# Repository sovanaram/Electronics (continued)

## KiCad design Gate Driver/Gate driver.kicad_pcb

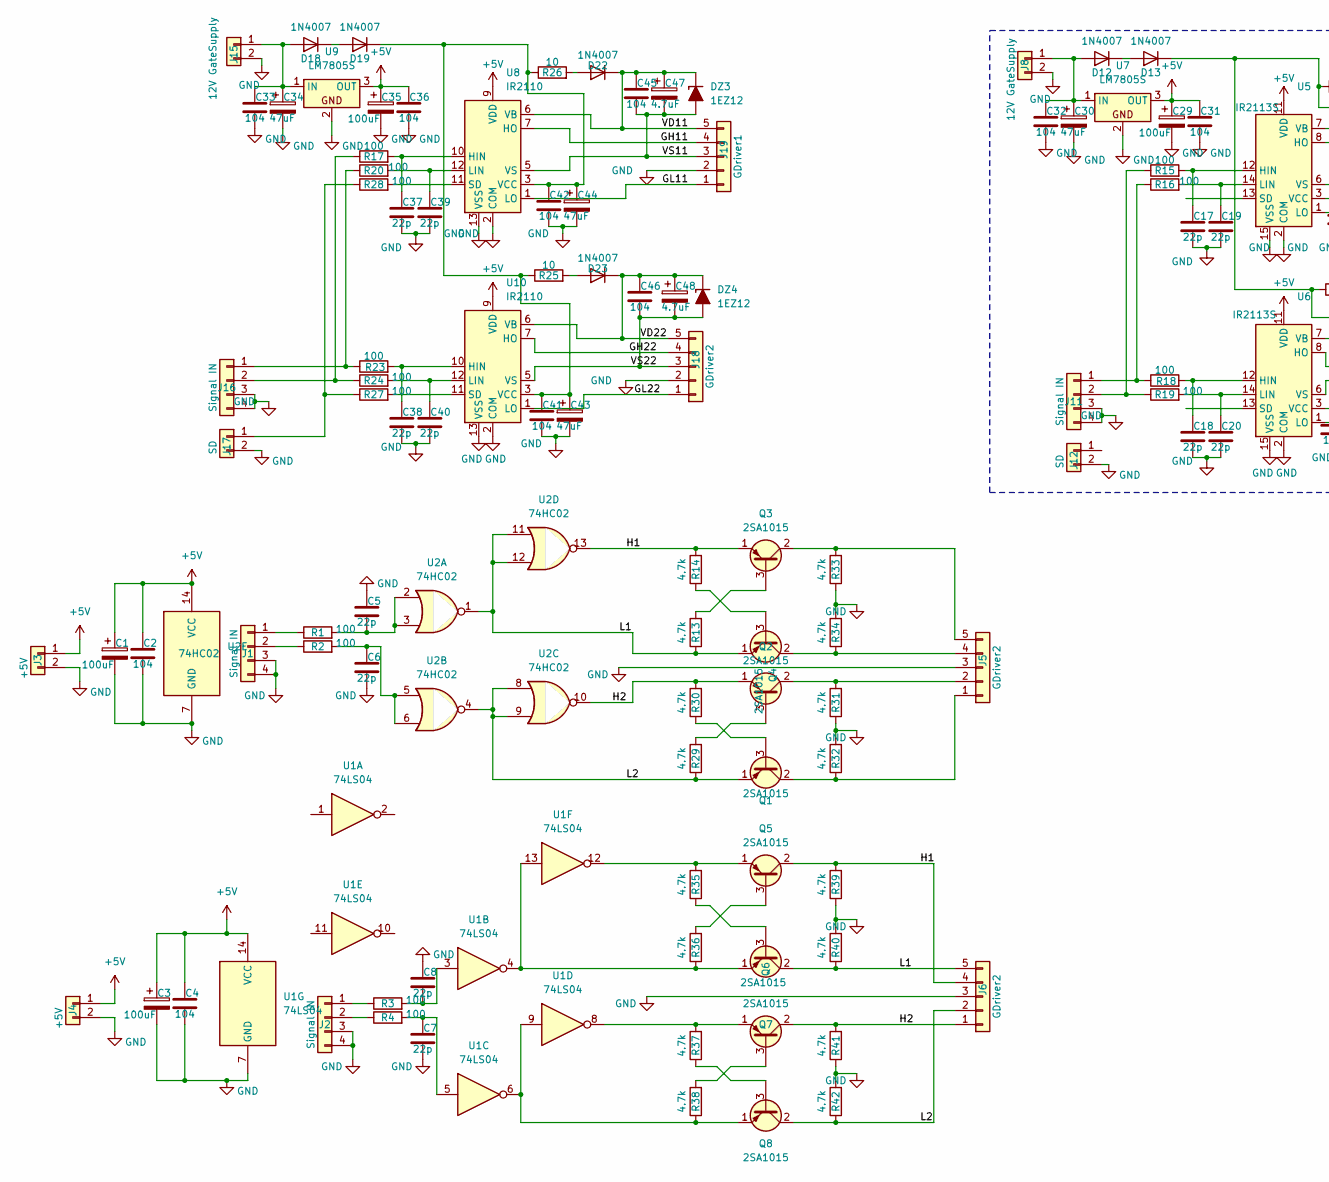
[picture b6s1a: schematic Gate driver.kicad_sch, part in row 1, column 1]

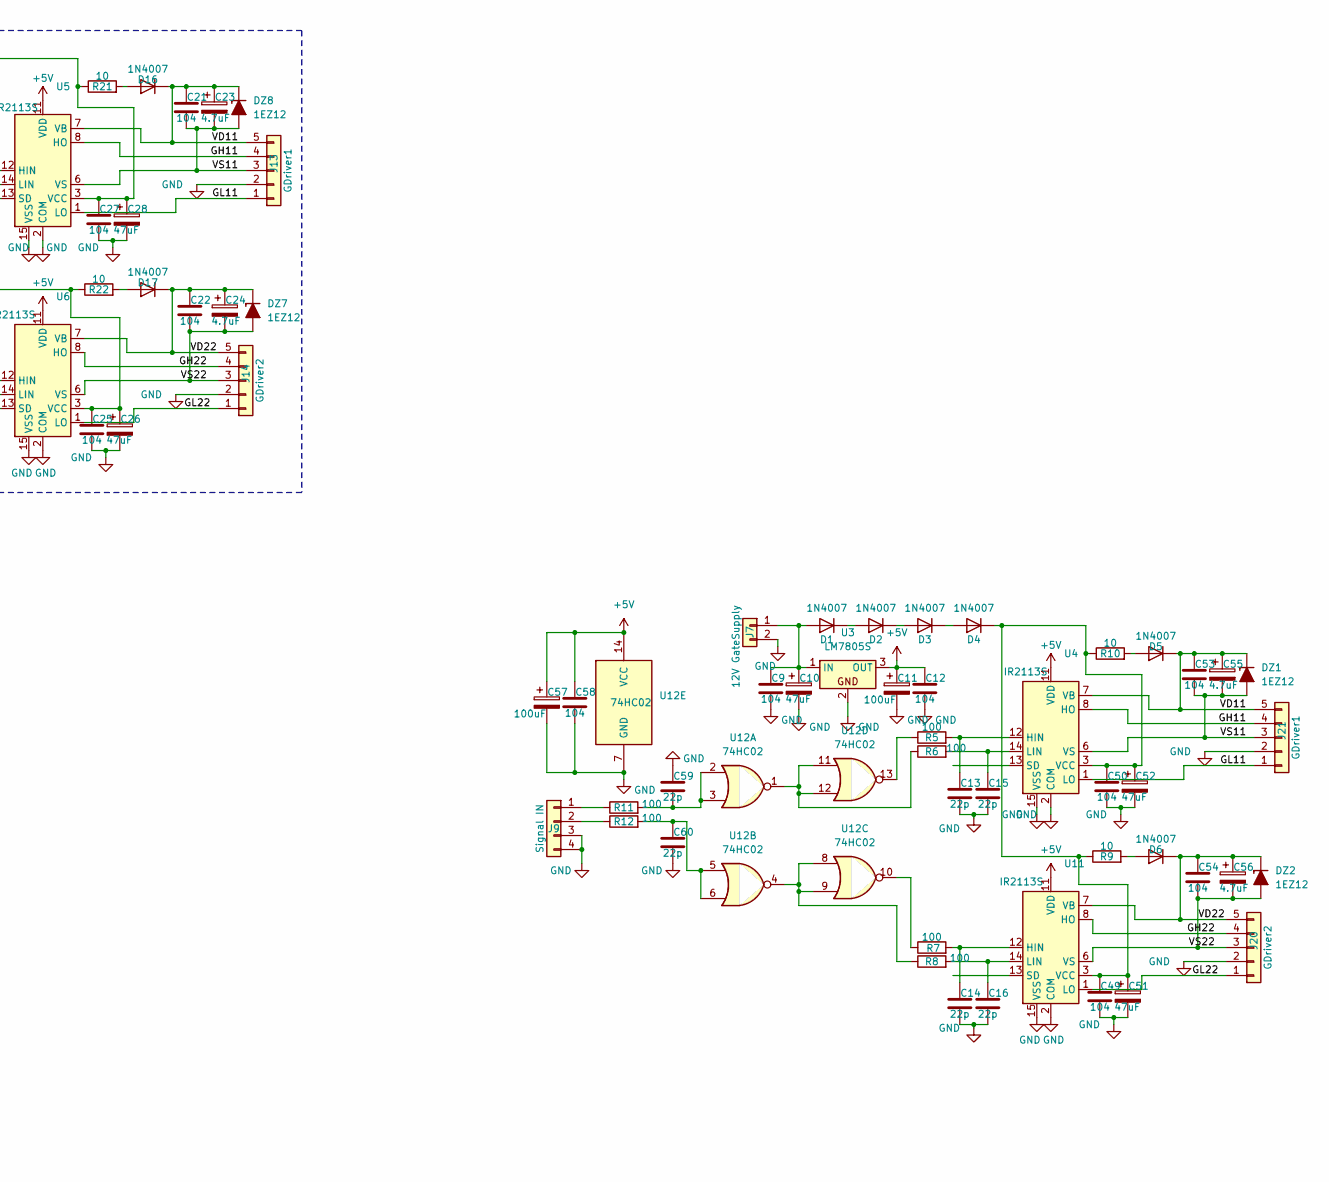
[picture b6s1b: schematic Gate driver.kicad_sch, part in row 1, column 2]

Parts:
C1, C3, C11, C29, C35, C57: 100uF; CP_Radial_D6.3mm_P2.50mm
C2, C4, C9, C12, C21, C22, C25, C27, C31, C32, C33, C36, C41, C42, C45, C46, C49, C50, C53, C54, C58: 104; C_Disc_D4.3mm_W1.9mm_P5.00mm
C5, C6, C7, C8, C13, C14, C15, C16, C17, C18, C19, C20, C37, C38, C39, C40, C59, C60: 22p; C_Disc_D4.3mm_W1.9mm_P5.00mm
C10, C26, C28, C30, C34, C43, C44, C51, C52: 47uF; CP_Radial_D6.3mm_P2.50mm
C23, C24, C47, C48, C55, C56: 4.7uF; CP_Radial_D6.3mm_P2.50mm
D1, D2, D3, D4, D5, D6, D12, D13, D16, D17, D18, D19, D22, D23: 1N4007; D_SMA
DZ1, DZ2, DZ3, DZ4, DZ7, DZ8: 1EZ12; D_DO-34_SOD68_P10.16mm_Horizontal
J1, J2, J9, J11, J16: Signal IN; JST_EH_B4B-EH-A_1x04_P2.50mm_Vertical
J3, J4: +5V; JST_EH_B2B-EH-A_1x02_P2.50mm_Vertical
J5, J6, J14, J18, J20: GDriver2; PinSocket_1x05_P2.54mm_Vertical
J7, J8, J15: 12V GateSupply; JST_EH_B2B-EH-A_1x02_P2.50mm_Vertical
J12, J17: SD; JST_EH_B2B-EH-A_1x02_P2.50mm_Vertical
J13, J19, J21: GDriver1; PinSocket_1x05_P2.54mm_Vertical
Q1, Q2, Q3, Q4, Q5, Q6, Q7, Q8: 2SA1015; TO-92_Inline_Wide_ECB
R1, R2, R3, R4, R5, R6, R7, R8, R11, R12, R15, R16, R17, R18, R19, R20, R23, R24, R27, R28: 100; R_Axial_DIN0207_L6.3mm_D2.5mm_P10.16mm_Horizontal
R9, R10, R21, R22, R25, R26: 10; R_1210_3225Metric_Pad1.30x2.65mm_HandSolder
R13, R14, R29, R30, R31, R32, R33, R34, R35, R36, R37, R38, R39, R40, R41, R42: 4.7k; R_Axial_DIN0207_L6.3mm_D2.5mm_P10.16mm_Horizontal
U1: 74LS04; DIP-14_W7.62mm_LongPads
U2, U12: 74HC02; DIP-14_W7.62mm_LongPads
U3, U7: LM7805S; TO-252-2
U4, U5, U6, U11: IR2113S; SOIC-16W_7.5x10.3mm_P1.27mm
U8, U10: IR2110; DIP-14_W7.62mm
U9: LM7805S; TO-263-3_TabPin2

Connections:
+5V: C1.1, C2.1, C3.1, C4.1, C11.1, C12.1, C29.1, C31.1, C35.1, C36.1, C57.1, C58.1, J3.1, J4.1, U1.14 (VCC), U2.14 (VCC), U3.3 (OUT), U4.11 (VDD), U5.11 (VDD), U6.11 (VDD), U7.3 (OUT), U8.9 (VDD), U9.3 (OUT), U10.9 (VDD), U11.11 (VDD), U12.14 (VCC)
/GH11: J13.4, J19.4, J21.4, U4.8 (HO), U5.8 (HO), U8.7 (HO)
/GH22: J14.4, J18.4, J20.4, U6.8 (HO), U10.7 (HO), U11.8 (HO)
/GL11: J13.1, J19.1, J21.1, U4.1 (LO), U5.1 (LO), U8.1 (LO)
/GL22: J14.1, J18.1, J20.1, U6.1 (LO), U10.1 (LO), U11.1 (LO)
/H1: J6.4, Q3.1 (E), Q5.2 (C), R14.2, R39.2, U2.13
/H2: J6.1, Q2.1 (E), Q7.2 (C), R30.2, R41.2, U2.10
/L1: J6.5, Q4.1 (E), Q6.2 (C), R13.1, R40.1, U2.1, U2.11, U2.12
/L2: J6.2, Q1.1 (E), Q8.2 (C), R29.1, R42.1, U2.4, U2.8, U2.9
/VD11: C21.1, C23.1, C45.1, C47.1, C53.1, C55.1, D5.1 (K), D16.1 (K), D22.1 (K), DZ1.1 (K), DZ3.1 (K), DZ8.1 (K), J13.5, J19.5, J21.5, U4.7 (VB), U5.7 (VB), U8.6 (VB)
/VS11: C21.2, C23.2, C45.2, C47.2, C53.2, C55.2, DZ1.2 (A), DZ3.2 (A), DZ8.2 (A), J13.3, J19.3, J21.3, U4.6 (VS), U5.6 (VS), U8.5 (VS)
GND: C1.2, C2.2, C3.2, C4.2, C5.1, C6.2, C7.2, C8.1, C9.2, C10.2, C11.2, C12.2, C13.2, C14.2, C15.2, C16.2, C17.2, C18.2, C19.2, C20.2, C25.2, C26.2, C27.2, C28.2, C29.2, C30.2, C31.2, C32.2, C33.2, C34.2, C35.2, C36.2, C37.2, C38.2, C39.2, C40.2, C41.2, C42.2, C43.2, C44.2, C49.2, C50.2, C51.2, C52.2, C57.2, C58.2, C59.1, C60.2, J1.3, J1.4, J2.3, J2.4, J3.2, J4.2, J5.3, J6.3, J7.2, J8.2, J9.3, J9.4, J11.3, J11.4, J12.2, J13.2, J14.2, J15.2, J16.3, J16.4, J17.2, J18.2, J19.2, J20.2, J21.2, R31.1, R32.2, R33.1, R34.2, R39.1, R40.2, R41.1, R42.2, U1.7 (GND), U2.7 (GND), U3.2, U4.2 (COM), U4.15 (VSS), U5.2 (COM), U5.15 (VSS), U6.2 (COM), U6.15 (VSS), U7.2, U8.2 (COM), U8.13 (VSS), U9.2, U10.2 (COM), U10.13 (VSS), U11.2 (COM), U11.15 (VSS), U12.7 (GND)
unnamed: C5.2, R1.2, U2.2, U2.3
unnamed: C6.1, R2.2, U2.5, U2.6
unnamed: C7.1, R4.2, U1.5
unnamed: C8.2, R3.2, U1.3
unnamed: C59.2, R11.2, U12.2, U12.3
unnamed: C60.1, R12.2, U12.5, U12.6
unnamed: C9.1, C10.1, D1.2 (A), J7.1, U3.1 (IN)
unnamed: D1.1 (K), D2.2 (A)
unnamed: D2.1 (K), D3.2 (A)
unnamed: D3.1 (K), D4.2 (A)
unnamed: C49.1, C50.1, C51.1, C52.1, D4.1 (K), R9.1, R10.1, U4.3 (VCC), U11.3 (VCC)
unnamed: D5.2 (A), R10.2
unnamed: D6.2 (A), R9.2
unnamed: C30.1, C32.1, D12.2 (A), J8.1, U7.1 (IN)
unnamed: D12.1 (K), D13.2 (A)
unnamed: D16.2 (A), R21.2
unnamed: D17.2 (A), R22.2
unnamed: C33.1, C34.1, D18.2 (A), J15.1, U9.1 (IN)
unnamed: D18.1 (K), D19.2 (A)
unnamed: D22.2 (A), R26.2
unnamed: D23.2 (A), R25.2
unnamed: J1.1, R1.1
unnamed: J1.2, R2.1
unnamed: J2.1, R3.1
unnamed: J2.2, R4.1
unnamed: J5.1, Q1.2 (C), R32.1
unnamed: J5.2, Q2.2 (C), R31.2
unnamed: J5.4, Q4.2 (C), R34.1
unnamed: J5.5, Q3.2 (C), R33.2
unnamed: J9.1, R11.1
unnamed: J9.2, R12.1
unnamed: J11.1, R16.1, R18.1
unnamed: J11.2, R15.1, R19.1
unnamed: J16.1, R20.1, R23.1
unnamed: J16.2, R17.1, R24.1
unnamed: J17.1, R27.1, R28.1
unnamed: Q1.3 (B), R30.1
unnamed: Q2.3 (B), R29.2
unnamed: Q3.3 (B), R13.2
unnamed: Q4.3 (B), R14.1
unnamed: Q5.3 (B), R36.2
unnamed: Q5.1 (E), R35.2, U1.12
unnamed: Q6.3 (B), R35.1
unnamed: Q6.1 (E), R36.1, U1.4, U1.13
unnamed: Q7.3 (B), R38.2
unnamed: Q7.1 (E), R37.2, U1.8
unnamed: Q8.3 (B), R37.1
unnamed: Q8.1 (E), R38.1, U1.6, U1.9
unnamed: R5.1, U12.13
unnamed: R6.1, U12.1, U12.11, U12.12
unnamed: R7.1, U12.10
unnamed: R8.1, U12.4, U12.8, U12.9
unnamed: C13.1, R5.2, U4.12 (HIN)
unnamed: C15.1, R6.2, U4.14 (LIN)
unnamed: C17.1, R15.2, U5.12 (HIN)
unnamed: C19.1, R16.2, U5.14 (LIN)
unnamed: C18.1, R18.2, U6.12 (HIN)
unnamed: C20.1, R19.2, U6.14 (LIN)
unnamed: C37.1, R17.2, U8.10 (HIN)
unnamed: C39.1, R20.2, U8.12 (LIN)
unnamed: R28.2, U8.11 (SD)
unnamed: C38.1, R23.2, U10.10 (HIN)
unnamed: C40.1, R24.2, U10.12 (LIN)
unnamed: R27.2, U10.11 (SD)
unnamed: C14.1, R7.2, U11.12 (HIN)
unnamed: C16.1, R8.2, U11.14 (LIN)

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
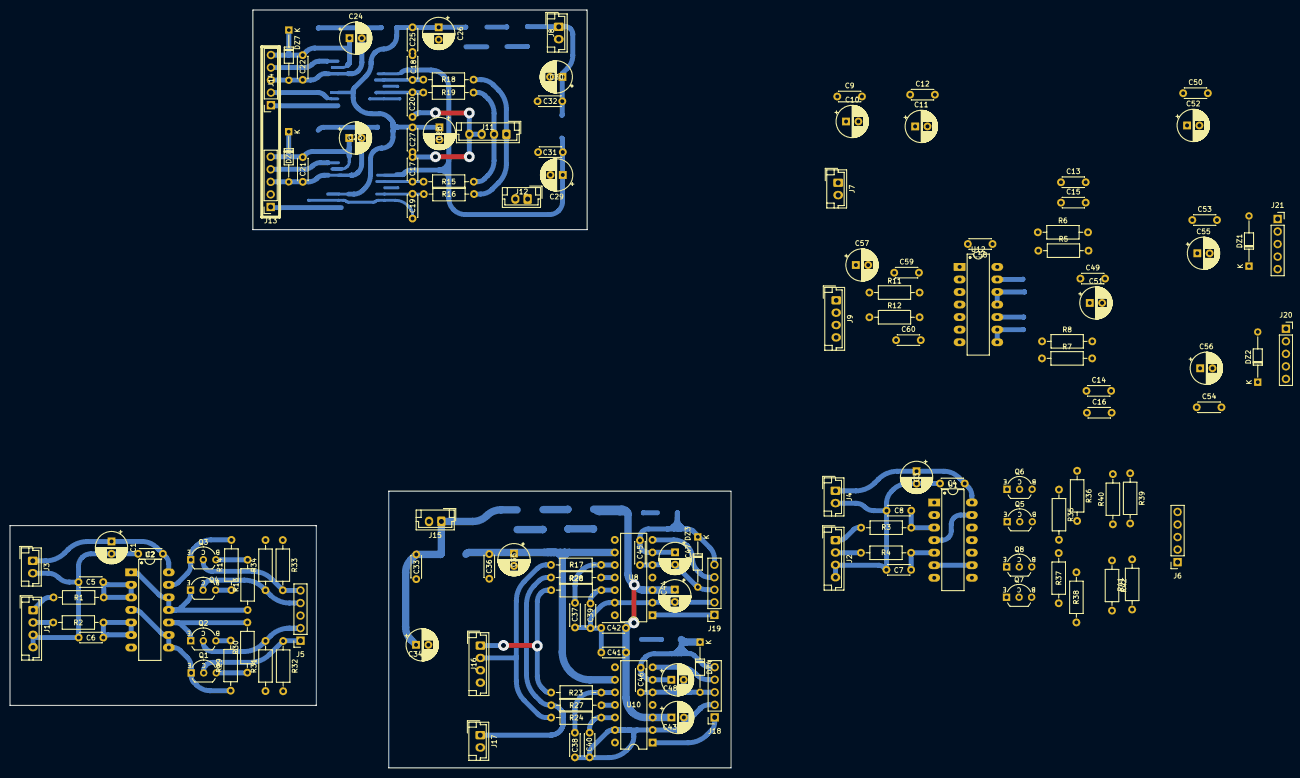
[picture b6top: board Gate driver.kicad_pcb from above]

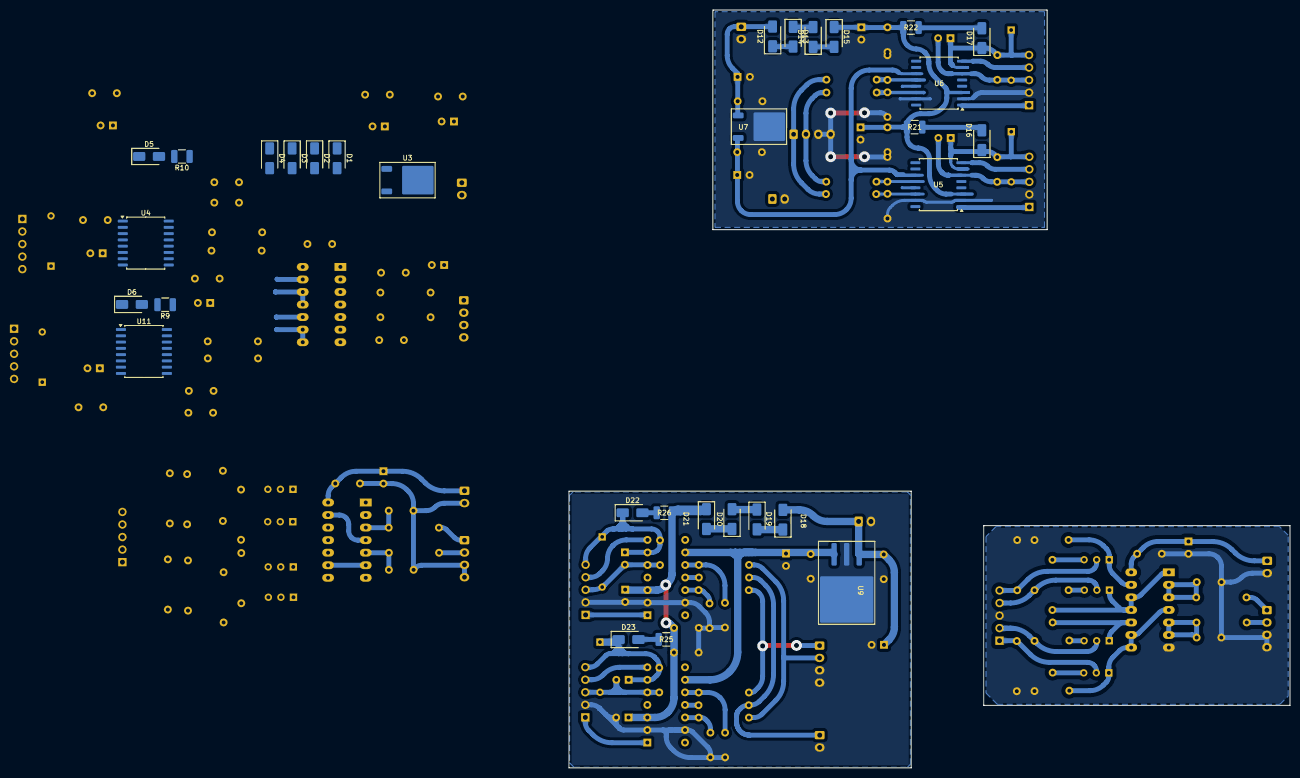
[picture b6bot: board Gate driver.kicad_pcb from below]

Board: 2 copper layers, 166 parts (31 on the bottom side), 86 nets.

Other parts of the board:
D14, D15, D20, D21: 1N4007; D_SMA

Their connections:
unnamed: D14.1 (K), D15.2 (A)
unnamed: D20.1 (K), D21.2 (A)

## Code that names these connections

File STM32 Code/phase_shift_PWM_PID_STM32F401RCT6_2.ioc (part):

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Mcu.Name=STM32F401R(B-C)Tx
Mcu.Package=LQFP64
Mcu.UserName=STM32F401RCTx
PA0-WKUP.Signal=ADCx_IN0
PA1.Signal=ADCx_IN1
PA10.Mode=Asynchronous
PA10.Signal=USART1_RX
PA13.Mode=Serial_Wire
PA13.Signal=SYS_JTMS-SWDIO
PA14.Mode=Serial_Wire
PA14.Signal=SYS_JTCK-SWCLK
PA2.Signal=ADCx_IN2
PA3.Signal=ADCx_IN3
PA4.Signal=ADCx_IN4
PA5.Signal=S_TIM2_CH1_ETR
PA8.Signal=S_TIM1_CH1
PA9.Mode=Asynchronous
PA9.Signal=USART1_TX
PB0.Signal=GPIO_Input
PB1.Signal=GPIO_Input
PB10.GPIOParameters=GPIO_PuPd
PB10.GPIO_PuPd=GPIO_PULLDOWN
PB10.Signal=GPIO_Input
PB12.Signal=GPIO_Output
PB13.Signal=GPIO_Output
PB14.Signal=GPIO_Output
PB15.Signal=GPIO_Output
PB2.Signal=GPIO_Input
PC13-ANTI_TAMP.Signal=GPIO_Output
PC14-OSC32_IN.Mode=LSE-External-Oscillator
PC14-OSC32_IN.Signal=RCC_OSC32_IN
PC15-OSC32_OUT.Mode=LSE-External-Oscillator
PC15-OSC32_OUT.Signal=RCC_OSC32_OUT
PH0\ -\ OSC_IN.Mode=HSE-External-Oscillator
PH0\ -\ OSC_IN.Signal=RCC_OSC_IN
PH1\ -\ OSC_OUT.Mode=HSE-External-Oscillator
PH1\ -\ OSC_OUT.Signal=RCC_OSC_OUT
RCC.HSE_VALUE=25000000
RCC.SYSCLKFreq_VALUE=84000000
RCC.SYSCLKSource=RCC_SYSCLKSOURCE_PLLCLK
board=custom

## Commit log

2024-12-08 Create h
2024-12-08 Create c
2024-12-08 Create C/C++
2024-12-08 Create cd
2024-12-08 Create d
2024-12-08 Create stm32
2024-12-08 Create RELAY 40A
2024-12-08 Create Isolated voltage sensor
2024-12-08 Create xcx
